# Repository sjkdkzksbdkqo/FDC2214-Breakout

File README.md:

# FDC2214-Breakout
4 Channel capacitive sensing based on the FDC2214 IC by TI

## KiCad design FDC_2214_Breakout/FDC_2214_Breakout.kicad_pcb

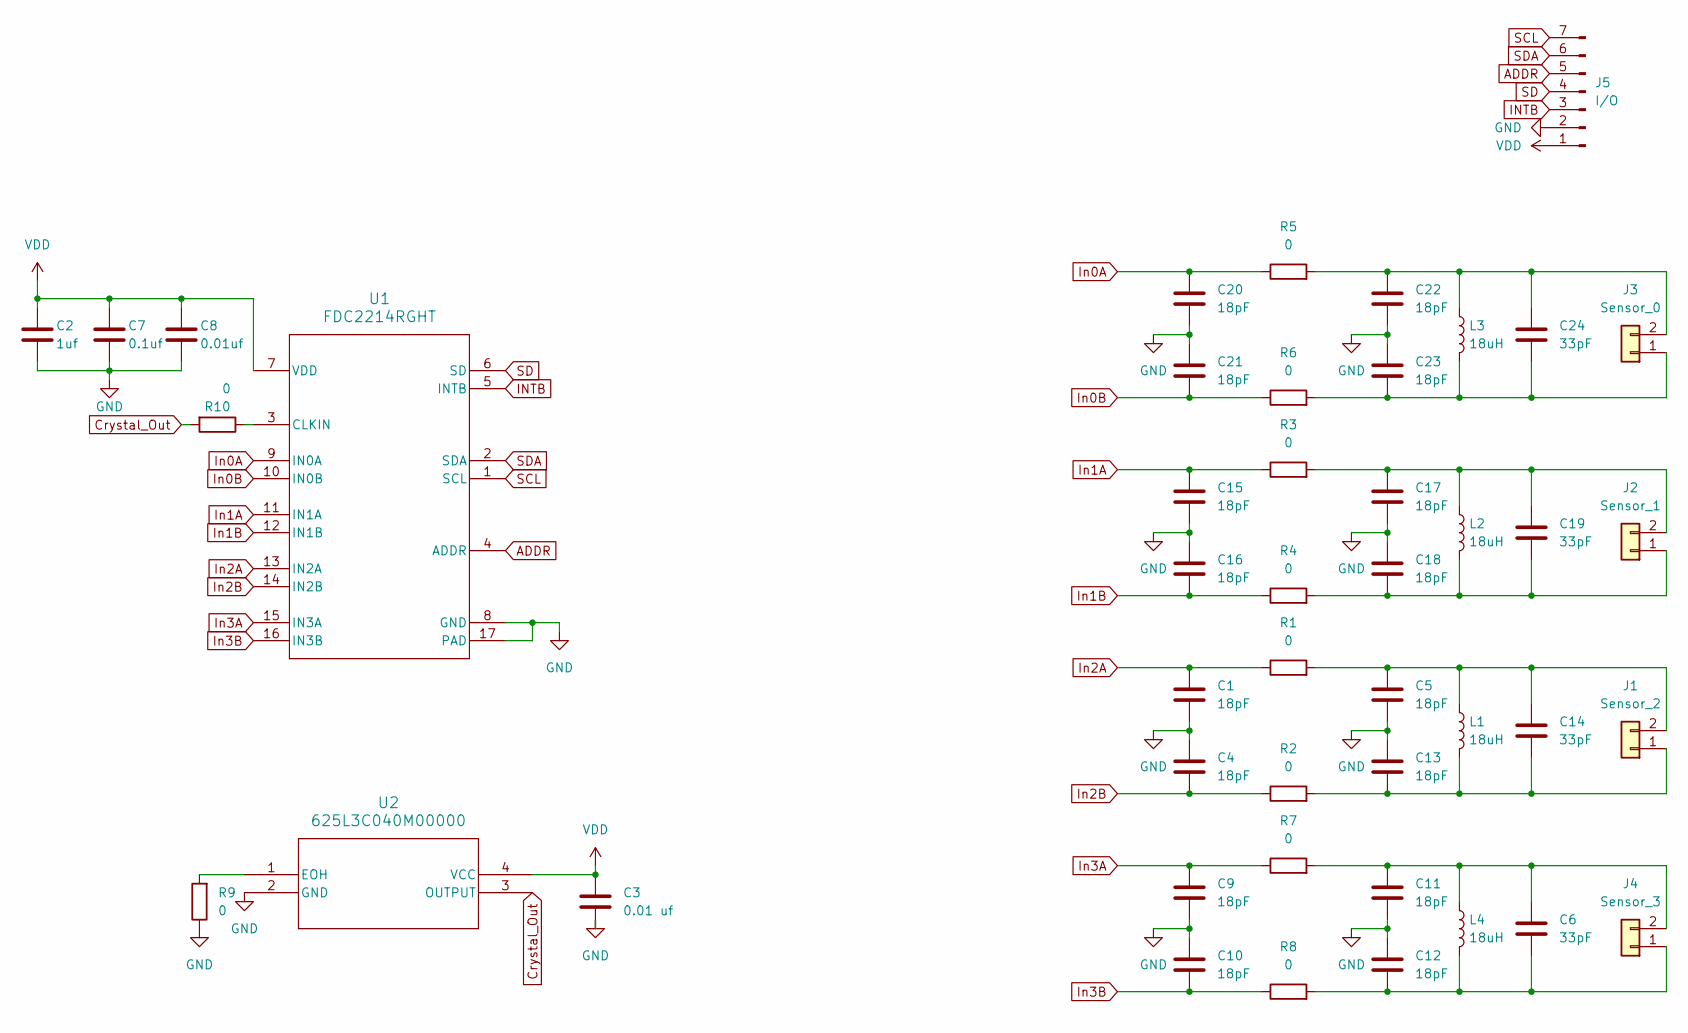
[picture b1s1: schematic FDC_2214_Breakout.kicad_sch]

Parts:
C1, C4, C5, C9, C10, C11, C12, C13, C15, C16, C17, C18, C20, C21, C22, C23: 18pF; C_0603
C2: 1uf; C_0603
C3: 0.01 uf; C_0603
C6, C14, C19, C24: 33pF; C_0805_2012Metric_Pad1.18x1.45mm_HandSolder
C7: 0.1uf; C_0603
C8: 0.01uf; C_0603
J1: Sensor_2; TerminalBlock_Phoenix_MPT-0,5-2-2.54_1x02_P2.54mm_Horizontal; Part Number 1-0201FBV0T
J2: Sensor_1; TerminalBlock_Phoenix_MPT-0,5-2-2.54_1x02_P2.54mm_Horizontal; Part Number 1-0201FBV0T
J3: Sensor_0; TerminalBlock_Phoenix_MPT-0,5-2-2.54_1x02_P2.54mm_Horizontal; Part Number 1-0201FBV0T
J4: Sensor_3; TerminalBlock_Phoenix_MPT-0,5-2-2.54_1x02_P2.54mm_Horizontal; Part Number 1-0201FBV0T
J5: I/O; PinHeader_1x07_P2.54mm_Vertical
L1, L2, L3, L4: 18uH; L_1210_3225Metric_Pad1.42x2.65mm_HandSolder
R1, R2, R3, R4, R5, R6, R7, R8, R9, R10: 0; R_0805_2012Metric_Pad1.20x1.40mm_HandSolder
U1: FDC2214RGHT; RGH0016A
U2: 625L3C040M00000; IC_625L3C040M00000_CTS-M

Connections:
ADDR: J5.5, U1.4 (ADDR)
Crystal_Out: R10.2, U2.3 (OUTPUT)
GND: C1.2, C2.1, C3.2, C4.1, C5.2, C7.1, C8.1, C9.2, C10.1, C11.2, C12.1, C13.1, C15.2, C16.1, C17.2, C18.1, C20.2, C21.1, C22.2, C23.1, J5.2, R9.1, U1.8 (GND), U1.17 (PAD), U2.2 (GND)
INTB: J5.3, U1.5 (INTB)
In0A: C20.1, R5.1, U1.9 (IN0A)
In0B: C21.2, R6.1, U1.10 (IN0B)
In1A: C15.1, R3.1, U1.11 (IN1A)
In1B: C16.2, R4.1, U1.12 (IN1B)
In2A: C1.1, R1.1, U1.13 (IN2A)
In2B: C4.2, R2.1, U1.14 (IN2B)
In3A: C9.1, R7.1, U1.15 (IN3A)
In3B: C10.2, R8.1, U1.16 (IN3B)
unnamed: C13.2, C14.2, J1.1, L1.2, R2.2
unnamed: C5.1, C14.1, J1.2, L1.1, R1.2
unnamed: C18.2, C19.2, J2.1, L2.2, R4.2
unnamed: C17.1, C19.1, J2.2, L2.1, R3.2
unnamed: C23.2, C24.2, J3.1, L3.2, R6.2
unnamed: C22.1, C24.1, J3.2, L3.1, R5.2
unnamed: C6.2, C12.2, J4.1, L4.2, R8.2
unnamed: C6.1, C11.1, J4.2, L4.1, R7.2
unnamed: R10.1, U1.3 (CLKIN)
unnamed: R9.2, U2.1 (EOH)
SCL: J5.7, U1.1 (SCL)
SD: J5.4, U1.6 (SD)
SDA: J5.6, U1.2 (SDA)
VDD: C2.2, C3.1, C7.2, C8.2, J5.1, U1.7 (VDD), U2.4 (VCC)

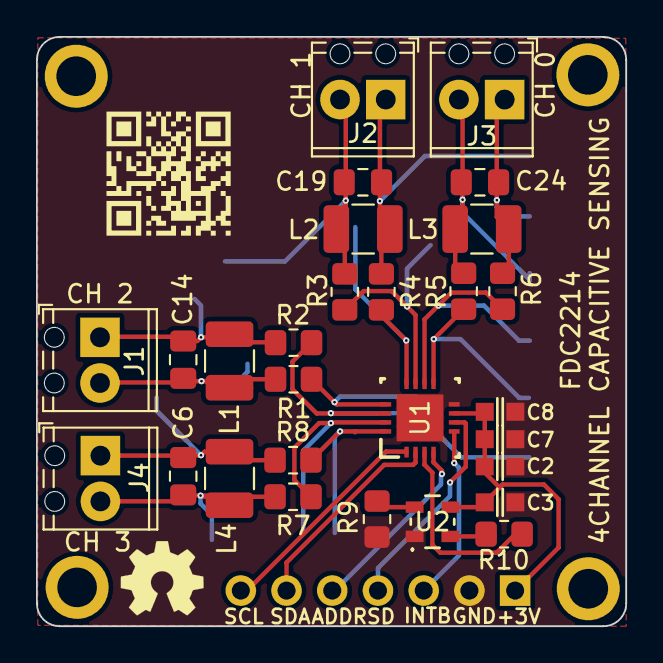
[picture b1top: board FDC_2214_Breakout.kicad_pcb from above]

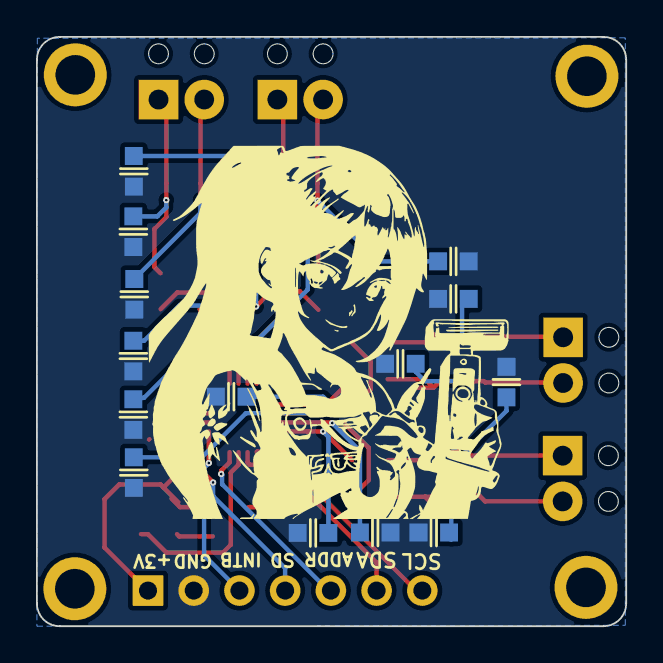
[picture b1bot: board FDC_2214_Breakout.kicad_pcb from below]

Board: 2 copper layers, 32.7 x 32.7 mm, 45 parts (16 on the bottom side), 26 nets.

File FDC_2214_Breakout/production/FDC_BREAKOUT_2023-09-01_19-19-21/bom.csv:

Designator,Footprint,Quantity,Value,LCSC Part #
"C1, C10, C11, C12, C13, C15, C16, C17, C18, C20, C21, C22, C23, C4, C5, C9",C_0805,16,18pF,
"C14, C19, C24, C6",0805,4,33pF,
C2,C_0603,1,1uf,
C3,C_0603,1,0.01 uf,
C7,C_0603,1,0.1uf,
C8,C_0603,1,0.01uf,
J1,"TerminalBlock_Phoenix_MPT-0,5-2-2.54_1x02_P2.54mm_Horizontal",1,Sensor_2,
J2,"TerminalBlock_Phoenix_MPT-0,5-2-2.54_1x02_P2.54mm_Horizontal",1,Sensor_1,
J3,"TerminalBlock_Phoenix_MPT-0,5-2-2.54_1x02_P2.54mm_Horizontal",1,Sensor_0,
J4,"TerminalBlock_Phoenix_MPT-0,5-2-2.54_1x02_P2.54mm_Horizontal",1,Sensor_3,
J5,PinHeader_1x07_P2.54mm_Vertical,1,I/O,
"L1, L2, L3, L4",1210,4,18uH,
"R1, R10, R2, R3, R4, R5, R6, R7, R8, R9",0805,10,0,
U1,RGH0016A,1,FDC2214RGHT,
U2,IC_625L3C040M00000_CTS-M,1,625L3C040M00000,

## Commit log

2023-09-02 Main_project
2023-09-05 Kicad Export
